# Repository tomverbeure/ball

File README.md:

# FreeCAD to KiCAD PCB outline export

    * Select face that you want as PCB outline
    * Make sure face is aligned with the view
    * With KiCAD StepUp plugin: project selected face to 2D
    * Convert 2D object to sketch
    * Export sketch to PCB layer

    * [Arranging PCB components in a circle with a script](http://kevincuzner.com/2017/04/28/arranging-components-in-a-circle-with-kicad/)

* Postprocessing

    * Chamfer alignment stickouts at the bottom (0.8mm)
    * Chamfer bottom of the triangle (1mm)
    * Fillet the 3 corners of the triangle (1mm)

# LED Sphere

* Isosahedron: 20 triangular faces

   Progression: 1, 1+3 = 4, 4 + 5 = 9, 9 + 7 = 16, 16 + 9 = 25, 25 + 11 = 36, 36 + 13 = 49

   * 1 triangle -> 1 triangle:    20 faces
   * 1 triangle -> 4 triangles:   80 faces
   * 1 triangle -> 9 triangles:  180 faces
   * 1 triangle -> 16 triangles: 320 faces
   * 1 triangle -> 25 triangles: 500 faces

Possibilities:

    * 80 faces, but divide each face into 16 LEDs -> 1280 LEDs
    * 80 faces, but divide each face into 25 LEDs -> 2000 LEDs
    * 80 faces, but divide each face into 36 LEDs -> 2880 LEDs
    * 80 faces, but divide each face into 49 LEDs -> 3920 LEDs

* 20 faces printed.

	* 2-sided triangle: 3  LEDs -> 60 LEDs
	* 3-sided triangle: 6  LEDs -> 120 LEDs
	* 4-sided triangle: 10 LEDs -> 200 LEDs
	* 5-sided triangle: 15 LEDs -> 300 
	* 6-sided triangle: 21 LEDs -> 420
	* 7-sided triangle: 27 LEDs -> 540
	* 8-sided triangle: 35 LEDs -> 700 

# Plug-in LEDs

* WS2812D-F8: $0.11 for 100+  

	* inner diameter: 8.0mm, outer diameter: 9.2mm
 	* [datasheet](https://datasheet.lcsc.com/lcsc/1811021523_Worldsemi-WS2812D-F8_C139126.pdf)
	* [LCSC](https://lcsc.com/product-detail/Light-Emitting-Diodes-span-style-background-color-ff0-LED-span_Worldsemi-WS2812D-F8_C139126.html)
	* 3.5V -> 5.3V
	* Needs capacitor and 75 Ohm resistor between VDD/GND per LED

* [75Ohm resistor](https://lcsc.com/product-detail/Chip-Resistor-Surface-Mount_FOJAN-FRC0603J750-TS_C2907204.html)
* [100nF cap](https://lcsc.com/product-detail/Multilayer-Ceramic-Capacitors-MLCC-SMD-SMT_FH-Guangdong-Fenghua-Advanced-Tech-0603B104K250NT_C694249.html)

# References

* [Geodesic(k) LED Spheres](https://blog.arduino.cc/2020/09/21/these-rgb-led-geodesic-spheres-are-stunning/)

    * [Build instructions](https://www.prusaprinters.org/prints/40182-geodesick-rgb-led-spheres)

* [Construct an icosahedron](https://www.youtube.com/watch?v=biq_SXjaoRU)

* [Construct an icosahedron in FreeCAD](https://www.youtube.com/watch?v=1VXpUjMM-_c)

* [Construction of regular icosahedron within a given sphere](https://proofwiki.org/wiki/Construction_of_Regular_Icosahedron_within_Given_Sphere)

    "From this it is manifest that the square on the diameter of the sphere is five times 
    the square on the radius of the circle from which the icosahedron has been described, 
    and that the diameter of the sphere is composed of the side of the pentagon and two of 
    the sides of the decagon inscribed in the same circle."

    Dsphere^2 = 5 * (Rpent^2)

    Rpent = sqrt(Dsphere^2/5) = Dsphere/sqrt(5) = 2 * Rsphere / sqrt(5)

* [Ad Quadratum Construction and Study of the Regular Polyhedra](http://www.lemeestudies.com/Misc/14.millennium_sphere/products/AdQuadratum.pdf)

* [Freecad scripting tutorial](https://wiki.freecadweb.org/Python_scripting_tutorial)

* [Freecad Topological data scripting](https://wiki.freecadweb.org/Topological_data_scripting)

# FreeCAD comments

* Base.Vector getAngle -> radians, all other functions -> degrees
* Simply viewing actions, such as aligning view to face are not present out of the box
* aligning a object along an axis is broken.
* Location of buttons in the toolbar always changes
* Add spheres for orientation
* FreeCAD over OpenSCAD: interactivity
* The number of LEDs must be chosen so that there's room in the center for a screw.

* When doing an align operation on a object that was created by an assembly of multiple identical components, 
  first create a Compound of it in Part.  Otherwise, the align seems to happen on the main component, not on the
  additional copies.

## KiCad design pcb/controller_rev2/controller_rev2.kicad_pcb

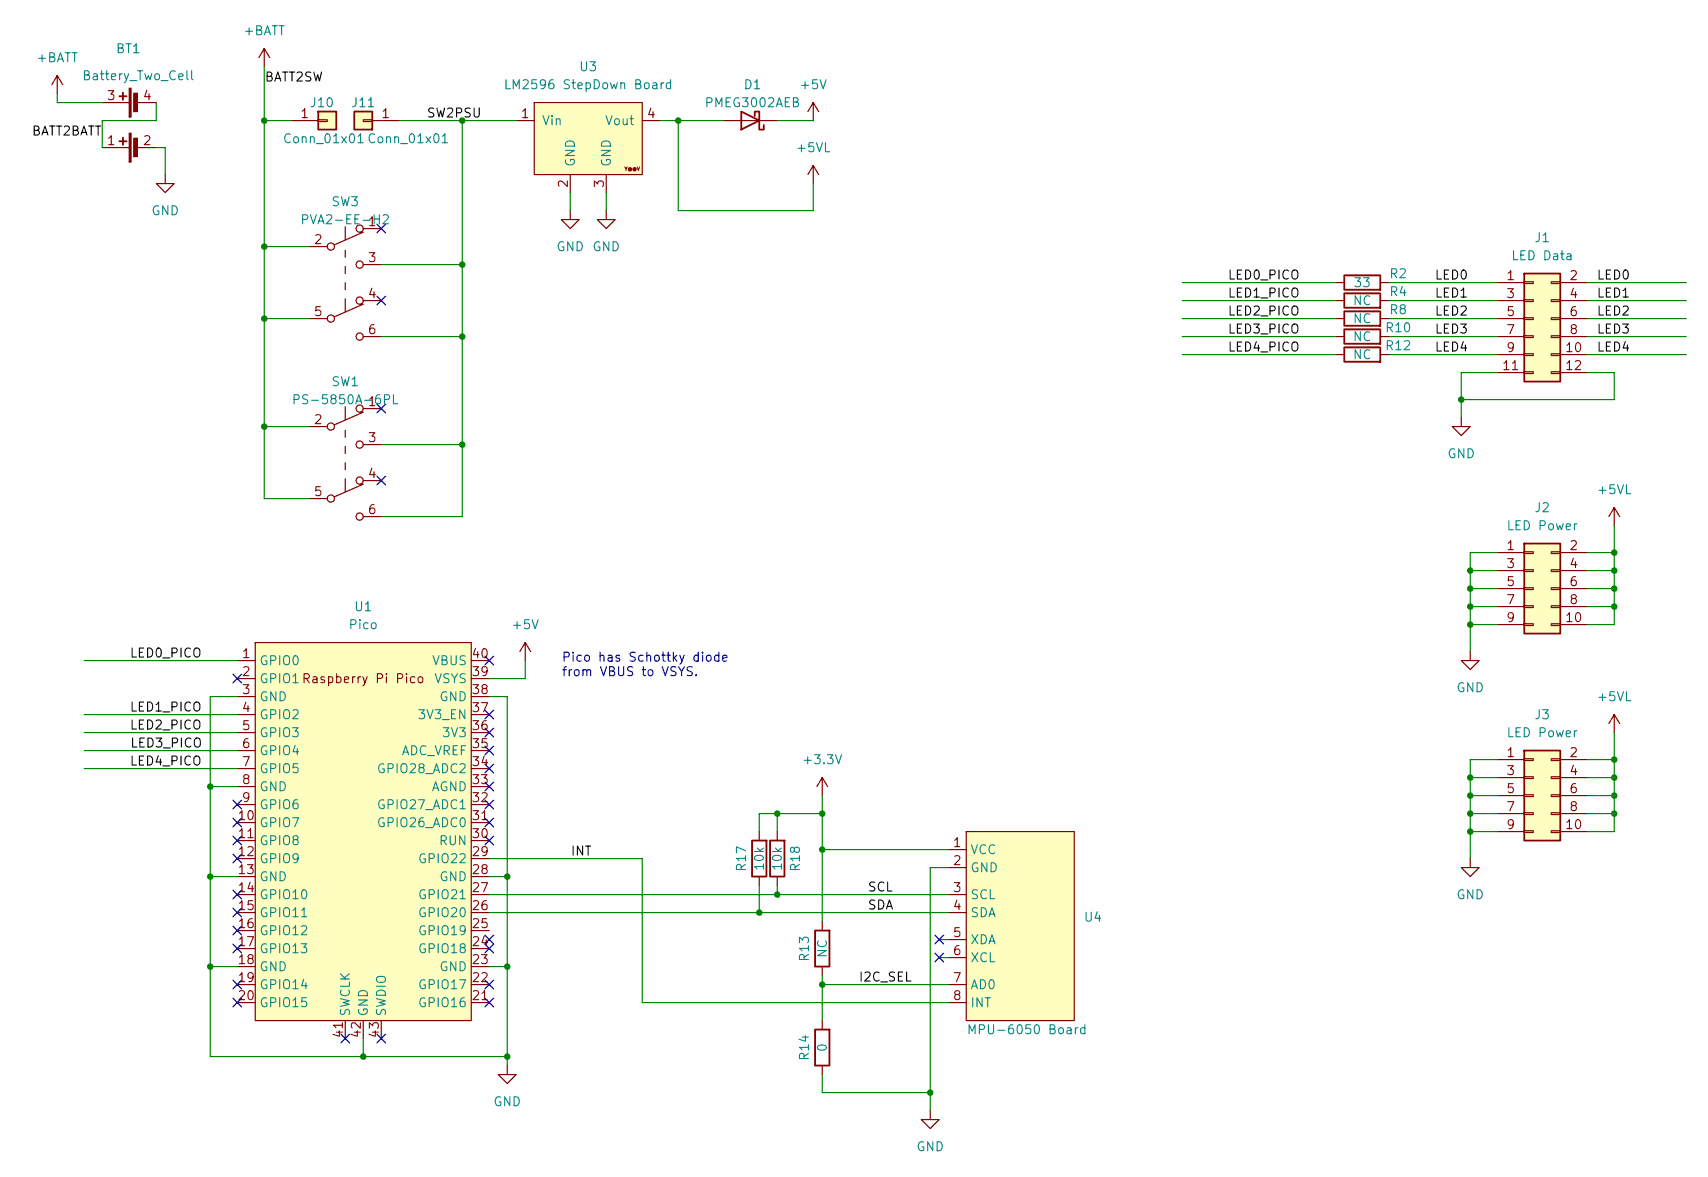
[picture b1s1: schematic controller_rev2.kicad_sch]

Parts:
BT1: Battery_Two_Cell; battery_holder
D1: PMEG3002AEB; D_SOD-523
J1: LED Data; PinHeader_2x06_P2.54mm_Vertical_SMD
J2, J3: LED Power; PinHeader_2x05_P2.54mm_Vertical_SMD
J10, J11: Conn_01x01; TestPoint_Loop_D3.80mm_Drill2.0mm
R2: 33; R_0603_1608Metric_Pad0.98x0.95mm_HandSolder
R4, R8, R10, R12, R13: NC; R_0603_1608Metric_Pad0.98x0.95mm_HandSolder
R14: 0; R_0603_1608Metric_Pad0.98x0.95mm_HandSolder
R17, R18: 10k; R_0603_1608Metric_Pad0.98x0.95mm_HandSolder
SW1: PS-5850A-6PL; SW_Push_2P2T_Toggle_G_Switch-PS-5850A-6PL
SW3: PVA2-EE-H2; SW_Push_2P2T_Toggle_CK_PVA2xxH2xxxxxxV2
U1: Pico; RPi_Pico_SMD_TH
U3: LM2596 StepDown Board; YAAJ_DCDC_StepDown_LM2596
U4: MPU-6050 Board; MPU-6050_Board_no_screw_holes

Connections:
+3V3: R13.2, R17.2, R18.2, U4.1 (VCC)
+5V: D1.1 (K), U1.39 (VSYS)
+5VL: D1.2 (A), J2.2, J2.4, J2.6, J2.8, J2.10, J3.2, J3.4, J3.6, J3.8, J3.10, U3.4 (Vout)
+BATT: BT1.3 (+), J10.1, SW1.2 (B), SW1.5 (B), SW3.2 (B), SW3.5 (B)
/BATT2BATT: BT1.1 (+), BT1.4 (-)
/I2C_SEL: R13.1, R14.2, U4.7 (AD0)
/INT: U1.29 (GPIO22), U4.8 (INT)
/LED0: J1.1, J1.2, R2.2
/LED0_PICO: R2.1, U1.1 (GPIO0)
/LED1: J1.3, J1.4, R4.2
/LED1_PICO: R4.1, U1.4 (GPIO2)
/LED2: J1.5, J1.6, R8.2
/LED2_PICO: R8.1, U1.5 (GPIO3)
/LED3: J1.7, J1.8, R10.2
/LED3_PICO: R10.1, U1.6 (GPIO4)
/LED4: J1.9, J1.10, R12.2
/LED4_PICO: R12.1, U1.7 (GPIO5)
/SCL: R18.1, U1.27 (GPIO21), U4.3 (SCL)
/SDA: R17.1, U1.26 (GPIO20), U4.4 (SDA)
/SW2PSU: J11.1, SW1.3 (C), SW1.6 (C), SW3.3 (C), SW3.6 (C), U3.1 (Vin)
GND: BT1.2 (-), J1.11, J1.12, J2.1, J2.3, J2.5, J2.7, J2.9, J3.1, J3.3, J3.5, J3.7, J3.9, R14.1, U1.3 (GND), U1.8 (GND), U1.13 (GND), U1.18 (GND), U1.23 (GND), U1.28 (GND), U1.38 (GND), U1.42 (GND), U3.2 (GND), U3.3 (GND), U4.2 (GND)

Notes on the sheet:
Pico has Schottky diode from VBUS to VSYS.

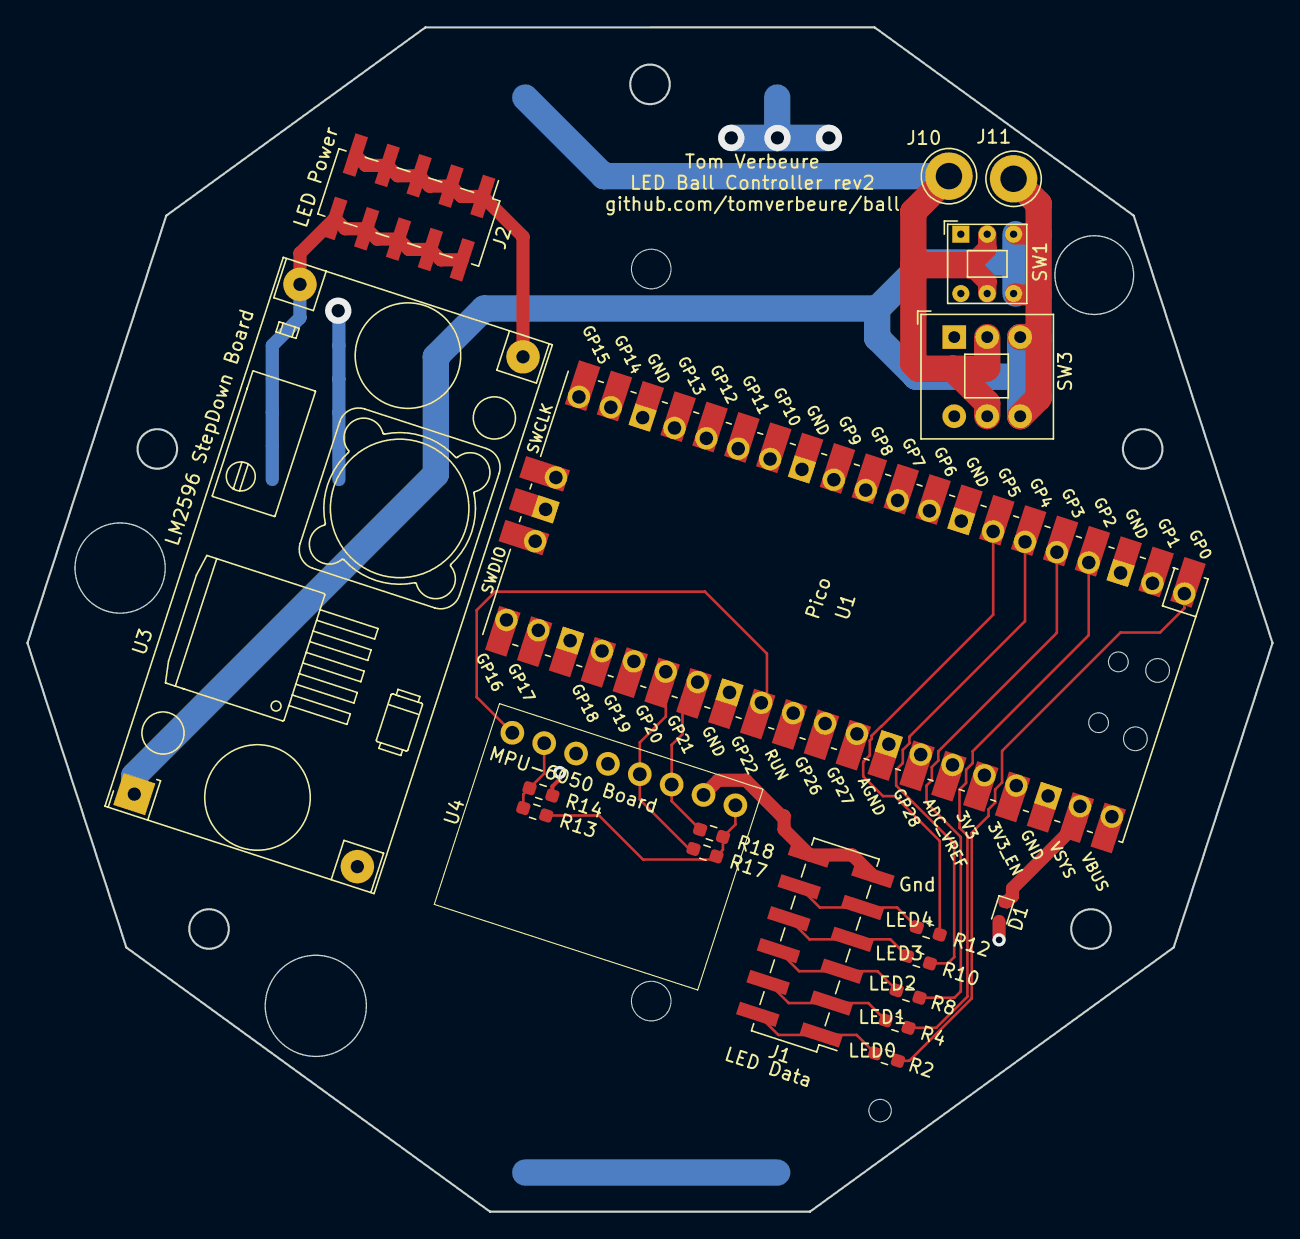
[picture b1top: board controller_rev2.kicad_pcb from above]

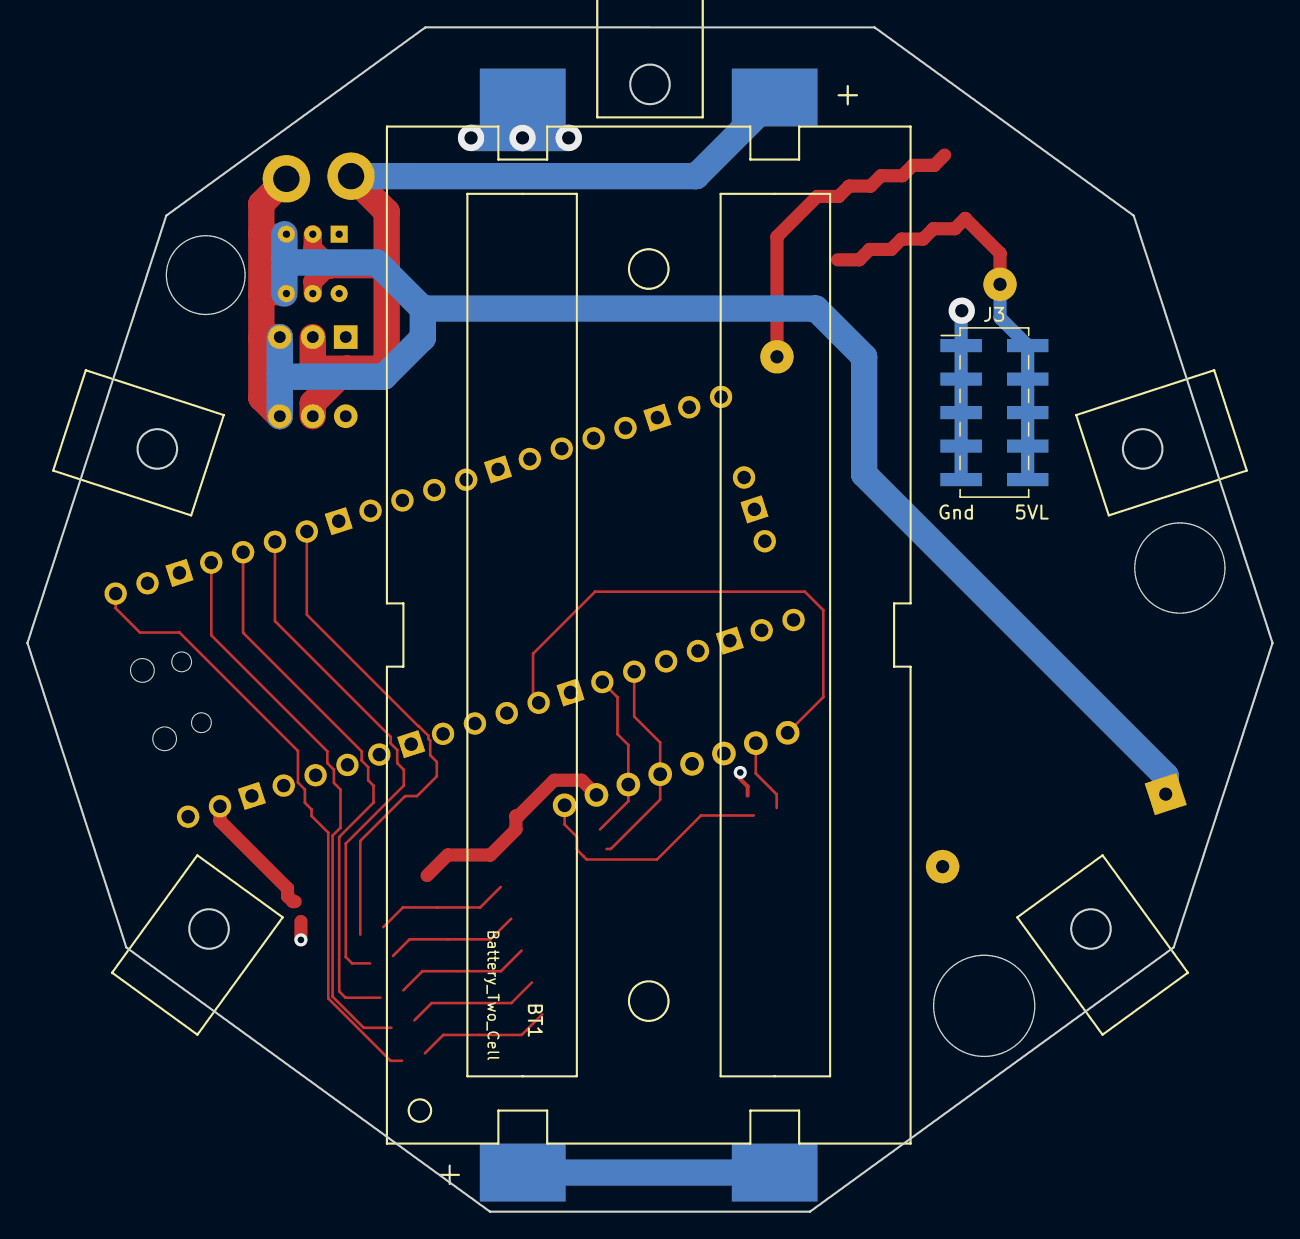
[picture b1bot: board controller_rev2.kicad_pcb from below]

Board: 4 copper layers, 94.4 x 89.8 mm, 21 parts (2 on the bottom side), 21 nets.

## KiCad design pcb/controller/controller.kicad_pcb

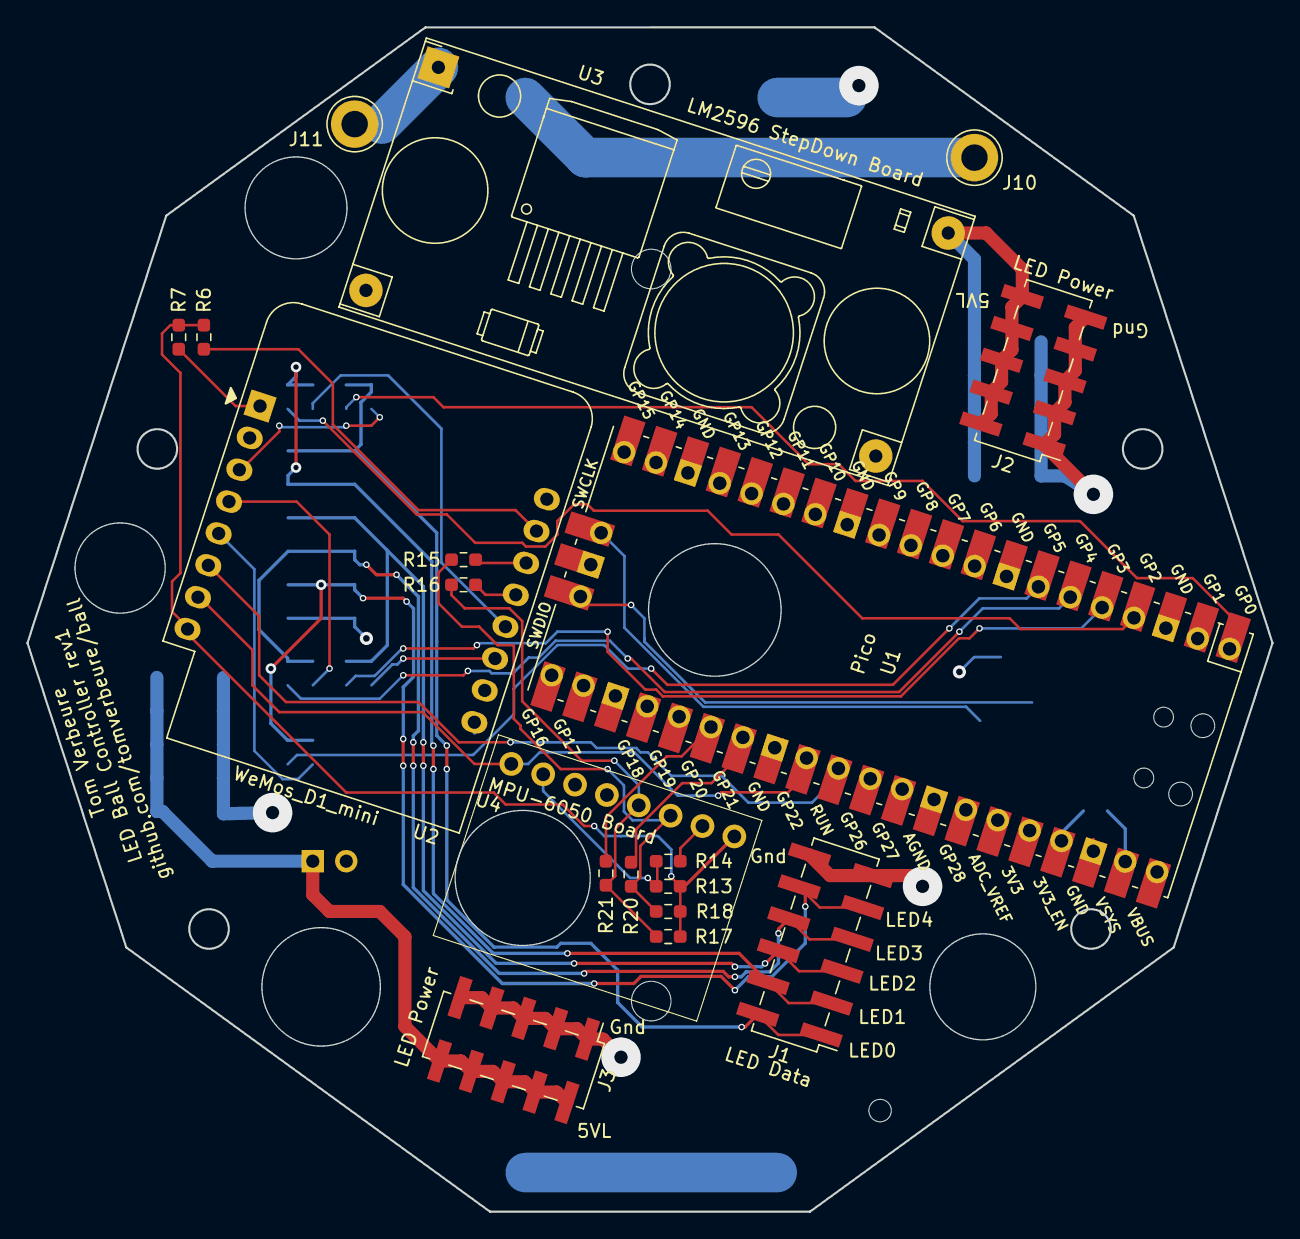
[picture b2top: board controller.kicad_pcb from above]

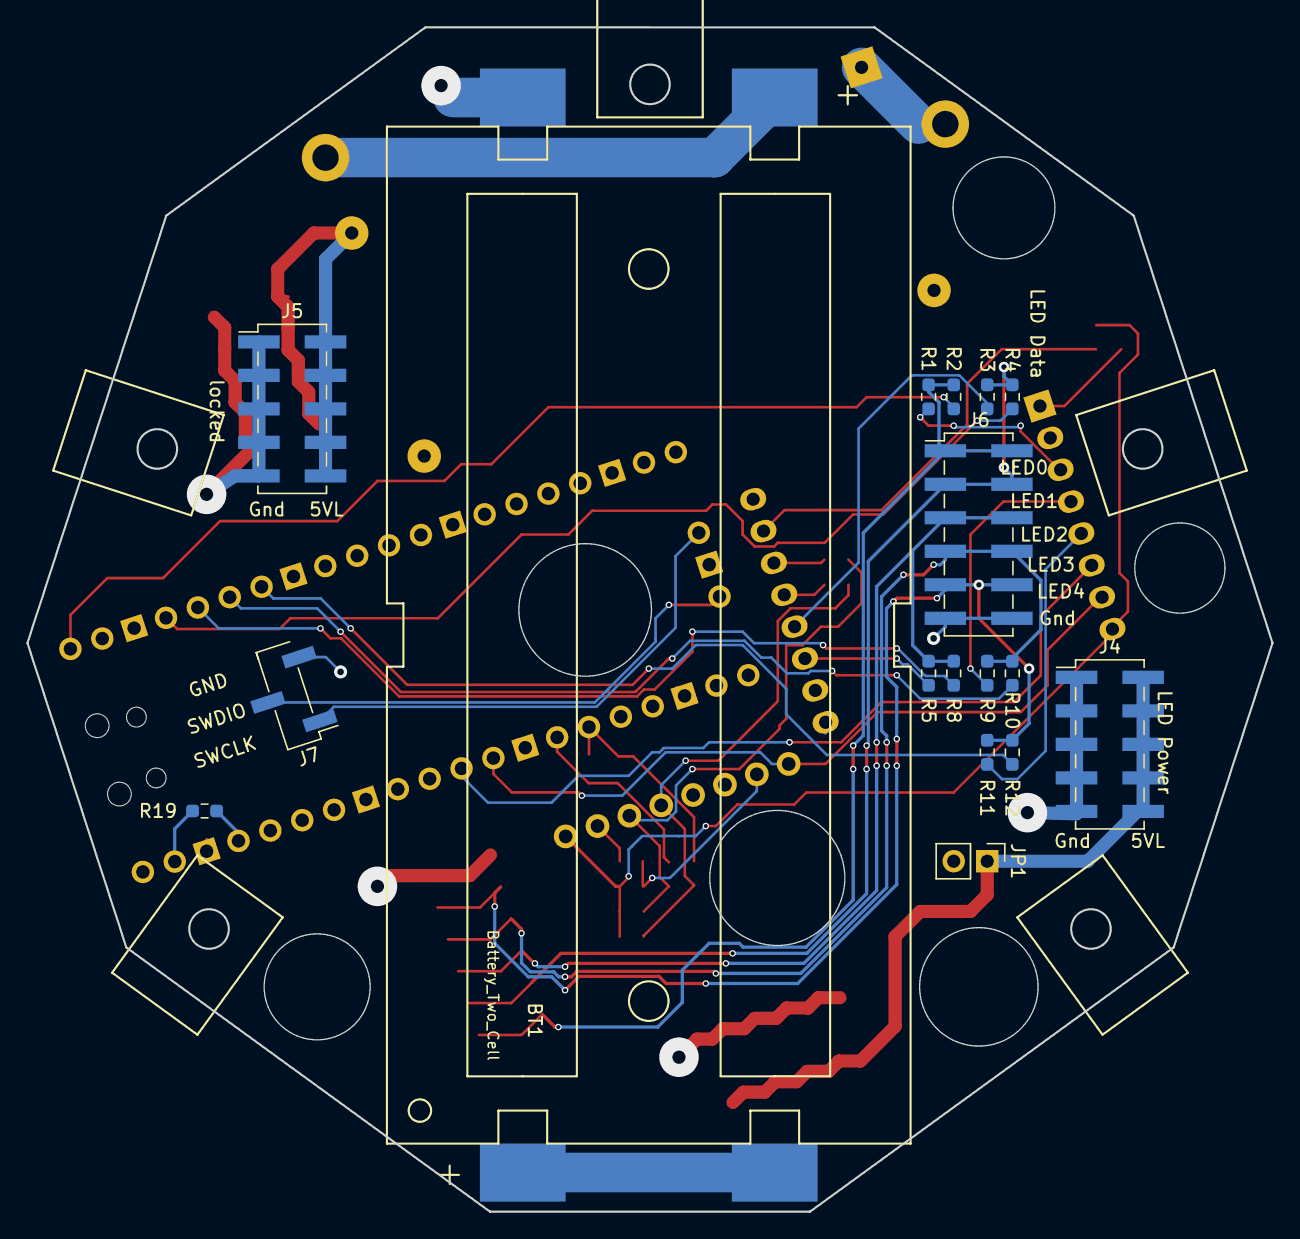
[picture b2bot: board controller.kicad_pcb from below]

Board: 4 copper layers, 94.4 x 89.8 mm, 36 parts (17 on the bottom side), 37 nets.

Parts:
BT1: Battery_Two_Cell; battery_holder
J1, J6: LED Data; PinHeader_2x06_P2.54mm_Vertical_SMD
J2, J3, J4: LED Power; PinHeader_2x05_P2.54mm_Vertical_SMD
J5: locked; PinHeader_2x05_P2.54mm_Vertical_SMD
J7: Conn_01x03_Male; PinHeader_1x03_P2.54mm_Vertical_SMD_Pin1Left
J10, J11: Conn_01x01; TestPoint_Loop_D3.80mm_Drill2.0mm
JP1: 5V Power; PinHeader_1x02_P2.54mm_Vertical
R1, R2, R3, R4, R5, R6, R7, R8, R9, R10, R11, R12, R13, R14, R17, R18: R; R_0603_1608Metric_Pad0.98x0.95mm_HandSolder
R15, R16, R19, R20, R21: 100K; R_0603_1608Metric_Pad0.98x0.95mm_HandSolder
U1: Pico; RPi_Pico_SMD_TH
U2: WeMos_D1_mini; WEMOS_D1_mini_light
U3: LM2596 StepDown Board; YAAJ_DCDC_StepDown_LM2596
U4: MPU-6050 Board; MPU-6050_Board_no_screw_holes

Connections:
+3V3: R6.1, R7.1, R13.2, R17.2, R18.2, U2.8 (3V3), U4.1 (VCC)
+5V: JP1.2 (B), U1.40 (VBUS), U2.9 (5V)
+5VL: J2.2, J2.4, J2.6, J2.8, J2.10, J3.2, J3.4, J3.6, J3.8, J3.10, J4.2, J4.4, J4.6, J4.8, J4.10, J5.2, J5.4, J5.6, J5.8, J5.10, JP1.1 (A), U3.4 (Vout)
+BATT: BT1.3 (+), J10.1
/BATT2BATT: BT1.1 (+), BT1.4 (-)
/INT: U1.29 (GPIO22), U2.7 (CS/D8), U4.8 (INT)
/LED0: J1.1, J1.2, J6.1, J6.2, R1.2, R2.2
/LED0_ESP: R1.1, U2.3 (D0)
/LED0_PICO: R2.1, U1.1 (GPIO0)
/LED1: J1.3, J1.4, J6.3, J6.4, R3.2, R4.2
/LED1_ESP: R3.1, U2.12 (D3)
/LED1_PICO: R4.1, U1.4 (GPIO2)
/LED2: J1.5, J1.6, J6.5, J6.6, R5.2, R8.2
/LED2_ESP: R5.1, U2.11 (D4)
/LED2_PICO: R8.1, U1.5 (GPIO3)
/LED3: J1.7, J1.8, J6.7, J6.8, R9.2, R10.2
/LED3_ESP: R9.1, U2.4 (SCK/D5)
/LED3_PICO: R10.1, U1.6 (GPIO4)
/LED4: J1.9, J1.10, J6.9, J6.10, R11.2, R12.2
/LED4_ESP: R11.1, U2.5 (MISO/D6)
/LED4_PICO: R12.1, U1.7 (GPIO5)
/PICO_RUN: U1.30 (RUN), U2.6 (MOSI/D7)
/SCL: R15.1, R18.1, R20.1, U4.3 (SCL)
/SDA: R16.1, R17.1, R21.1, U4.4 (SDA)
/SW2PSU: J11.1, U3.1 (Vin)
/SWCLK: J7.1, U1.41 (SWCLK)
/SWDIO: J7.2, U1.43 (SWDIO)
GND: BT1.2 (-), J1.11, J1.12, J2.1, J2.3, J2.5, J2.7, J2.9, J3.1, J3.3, J3.5, J3.7, J3.9, J4.1, J4.3, J4.5, J4.7, J4.9, J5.1, J5.3, J5.5, J5.7, J5.9, J6.11, J6.12, J7.3, R14.1, U1.3 (GND), U1.8 (GND), U1.18 (GND), U1.23 (GND), U1.28 (GND), U1.38 (GND), U1.42 (GND), U2.10 (GND), U3.2 (GND), U3.3 (GND), U4.2 (GND)
unnamed: R6.2, U2.15 (RX)
unnamed: R7.2, U2.1 (~RST)
unnamed: R13.1, R14.2, U4.7 (AD0)
unnamed: R15.2, U2.14 (SCL/D1)
unnamed: R16.2, U2.13 (SDA/D2)
unnamed: R19.1, U1.39 (VSYS)
unnamed: R19.2, U1.37 (3V3_EN)
unnamed: R20.2, U1.27 (GPIO21)
unnamed: R21.2, U1.26 (GPIO20)

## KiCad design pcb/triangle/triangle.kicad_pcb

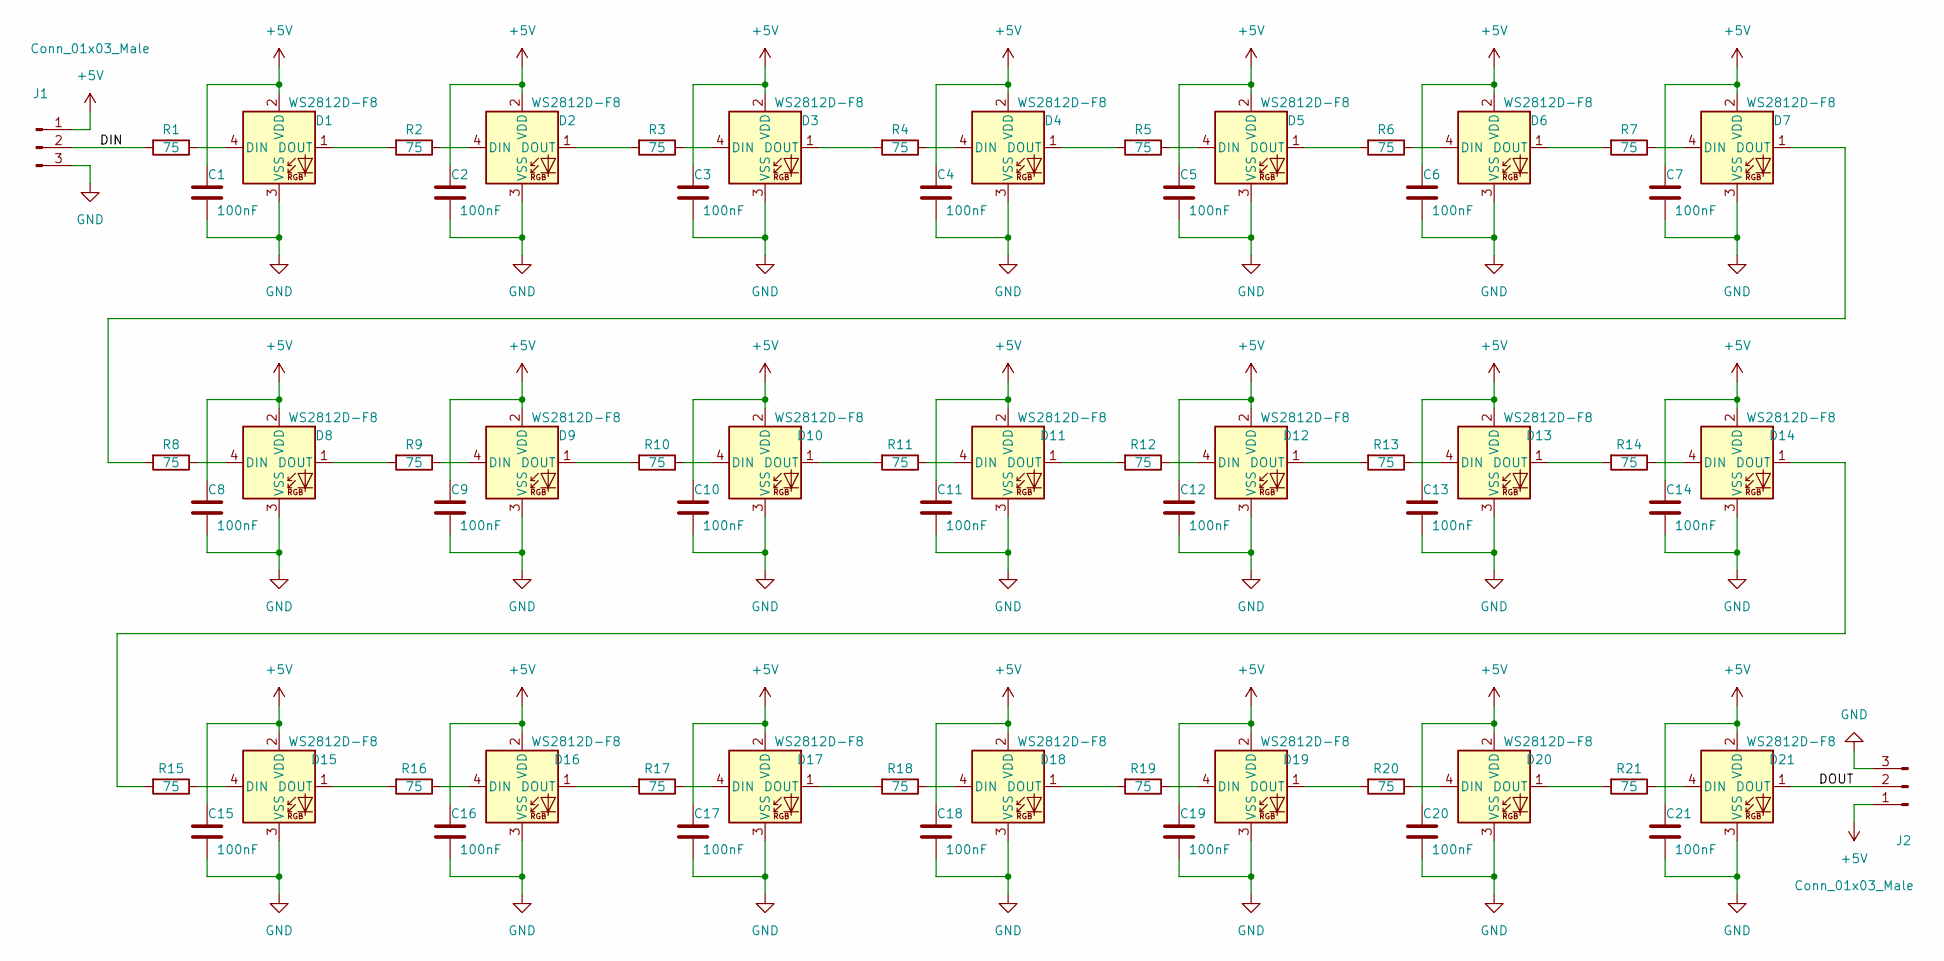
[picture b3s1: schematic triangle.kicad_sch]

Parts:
C1, C2, C3, C4, C5, C6, C7, C8, C9, C10, C11, C12, C13, C14, C15, C16, C17, C18, C19, C20, C21: 100nF; C_0603_1608Metric
D1, D2, D3, D4, D5, D6, D7, D8, D9, D10, D11, D12, D13, D14, D15, D16, D17, D18, D19, D20, D21: WS2812D-F8; LED_D8.0mm-4
J1, J2: Conn_01x03_Male; PinHeader_1x03_P2.54mm_Vertical
R1, R2, R3, R4, R5, R6, R7, R8, R9, R10, R11, R12, R13, R14, R15, R16, R17, R18, R19, R20, R21: 75; R_0603_1608Metric

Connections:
+5V: C1.1, C2.1, C3.1, C4.1, C5.1, C6.1, C7.1, C8.1, C9.1, C10.1, C11.1, C12.1, C13.1, C14.1, C15.1, C16.1, C17.1, C18.1, C19.1, C20.1, C21.1, D1.2 (VDD), D2.2 (VDD), D3.2 (VDD), D4.2 (VDD), D5.2 (VDD), D6.2 (VDD), D7.2 (VDD), D8.2 (VDD), D9.2 (VDD), D10.2 (VDD), D11.2 (VDD), D12.2 (VDD), D13.2 (VDD), D14.2 (VDD), D15.2 (VDD), D16.2 (VDD), D17.2 (VDD), D18.2 (VDD), D19.2 (VDD), D20.2 (VDD), D21.2 (VDD), J1.1, J2.1
/DIN: J1.2, R1.2
/DOUT: D21.1 (DOUT), J2.2
GND: C1.2, C2.2, C3.2, C4.2, C5.2, C6.2, C7.2, C8.2, C9.2, C10.2, C11.2, C12.2, C13.2, C14.2, C15.2, C16.2, C17.2, C18.2, C19.2, C20.2, C21.2, D1.3 (VSS), D2.3 (VSS), D3.3 (VSS), D4.3 (VSS), D5.3 (VSS), D6.3 (VSS), D7.3 (VSS), D8.3 (VSS), D9.3 (VSS), D10.3 (VSS), D11.3 (VSS), D12.3 (VSS), D13.3 (VSS), D14.3 (VSS), D15.3 (VSS), D16.3 (VSS), D17.3 (VSS), D18.3 (VSS), D19.3 (VSS), D20.3 (VSS), D21.3 (VSS), J1.3, J2.3
unnamed: D1.1 (DOUT), R2.2
unnamed: D1.4 (DIN), R1.1
unnamed: D2.1 (DOUT), R3.2
unnamed: D2.4 (DIN), R2.1
unnamed: D3.1 (DOUT), R4.2
unnamed: D3.4 (DIN), R3.1
unnamed: D4.1 (DOUT), R5.2
unnamed: D4.4 (DIN), R4.1
unnamed: D5.1 (DOUT), R6.2
unnamed: D5.4 (DIN), R5.1
unnamed: D6.1 (DOUT), R7.2
unnamed: D6.4 (DIN), R6.1
unnamed: D7.1 (DOUT), R8.2
unnamed: D7.4 (DIN), R7.1
unnamed: D8.1 (DOUT), R9.2
unnamed: D8.4 (DIN), R8.1
unnamed: D9.1 (DOUT), R10.2
unnamed: D9.4 (DIN), R9.1
unnamed: D10.1 (DOUT), R11.2
unnamed: D10.4 (DIN), R10.1
unnamed: D11.1 (DOUT), R12.2
unnamed: D11.4 (DIN), R11.1
unnamed: D12.1 (DOUT), R13.2
unnamed: D12.4 (DIN), R12.1
unnamed: D13.1 (DOUT), R14.2
unnamed: D13.4 (DIN), R13.1
unnamed: D14.1 (DOUT), R15.2
unnamed: D14.4 (DIN), R14.1
unnamed: D15.1 (DOUT), R16.2
unnamed: D15.4 (DIN), R15.1
unnamed: D16.1 (DOUT), R17.2
unnamed: D16.4 (DIN), R16.1
unnamed: D17.1 (DOUT), R18.2
unnamed: D17.4 (DIN), R17.1
unnamed: D18.1 (DOUT), R19.2
unnamed: D18.4 (DIN), R18.1
unnamed: D19.1 (DOUT), R20.2
unnamed: D19.4 (DIN), R19.1
unnamed: D20.1 (DOUT), R21.2
unnamed: D20.4 (DIN), R20.1
unnamed: D21.4 (DIN), R21.1

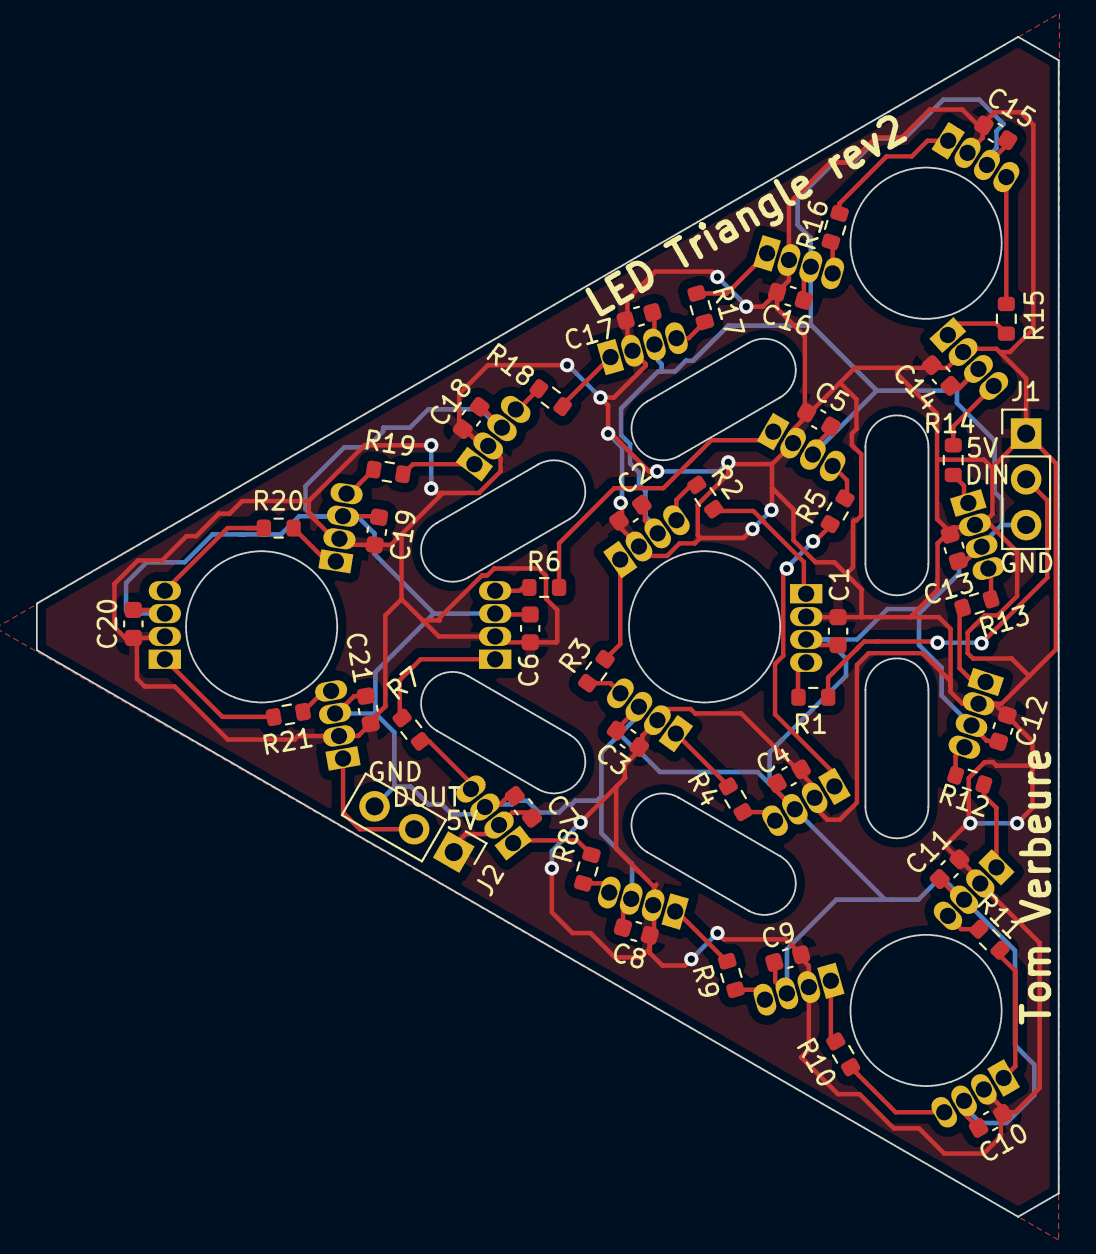
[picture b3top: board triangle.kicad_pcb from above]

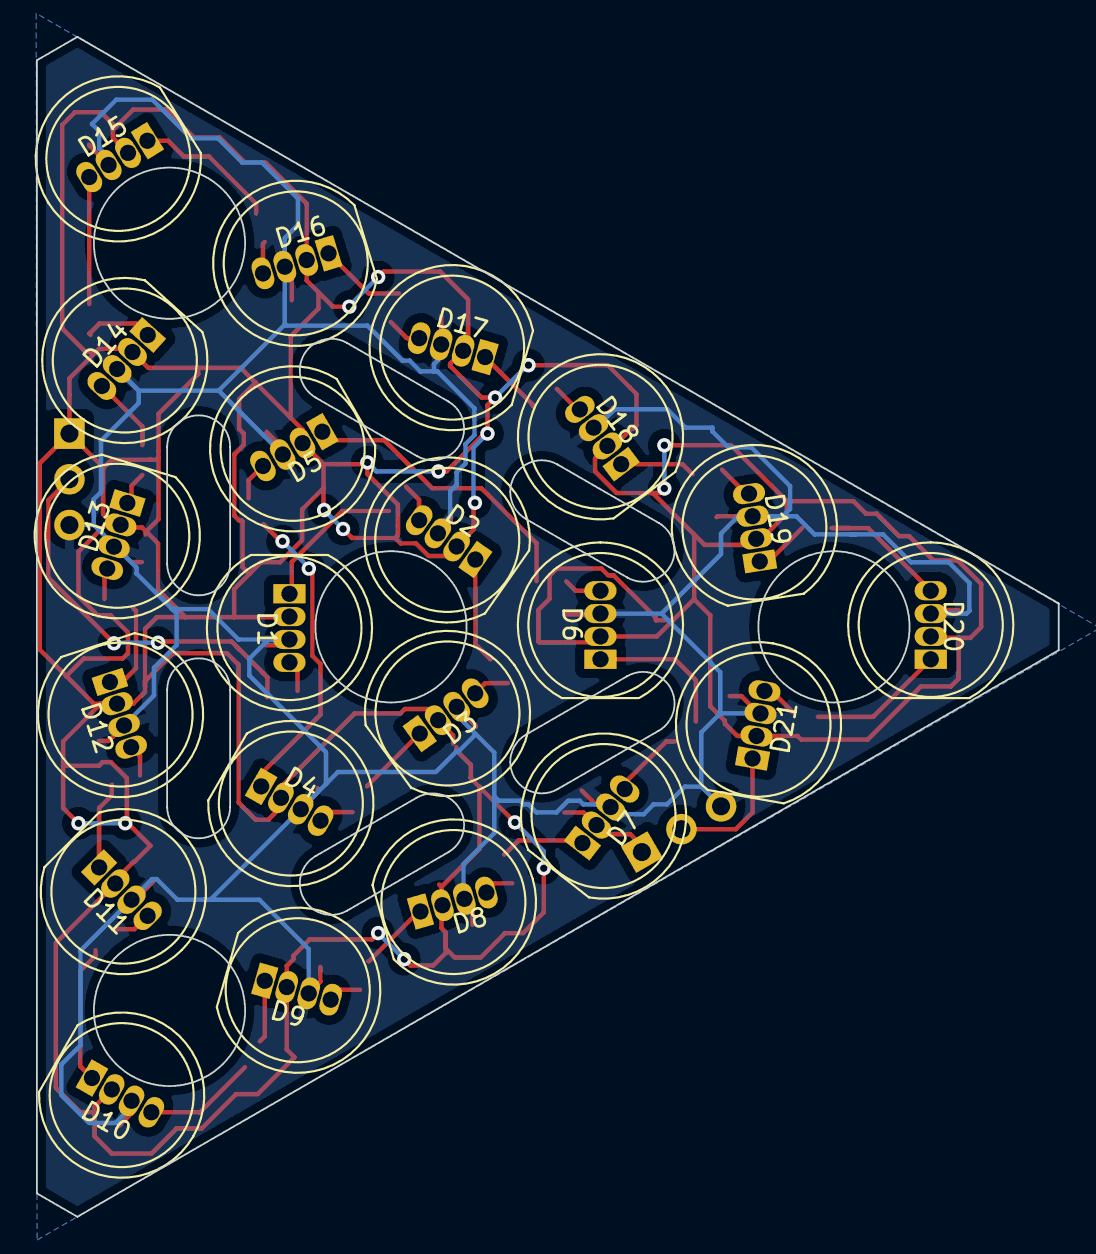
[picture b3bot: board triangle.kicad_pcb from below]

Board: 2 copper layers, 56.8 x 65.5 mm, 65 parts (21 on the bottom side), 45 nets.

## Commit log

2019-09-07 Hexagon
2019-09-07 Add hole.
2019-09-07 Move icosahedron experiment to its own directory.
2019-09-07 C healpix
2019-09-07 Sphere with healpix pixels
2019-09-07 Make sphere green.
2019-09-07 Dots colors per face.
2019-09-08 Patch chealpix for xyv2nest function.
2019-09-08 Polyhedron fail.
2019-09-08 Boundary of face 0.
2019-09-08 4 top cut boundaries.
2019-09-08 Move some code scene_py.py
2019-09-08 Move led rendering to python.
2021-12-22 Assembly with uneven holes. (Use as bad example 1.)
2021-12-22 Move around.
2021-12-22 10 LEDs per face, spread roughly evenly.
2022-01-08 Various trials.
2022-01-09 Radiating screw holes.
2022-01-10 Assembly.
2022-01-18 Start of script.
2022-01-20 Checkpoint. Use Draft.point to rotate.
2022-01-20 Calculate LED locations
2022-01-20 Create LED holes.
2022-01-21 Cut sphere into rounded tetrahedron.
2022-01-22 line plane intersection
2022-01-22 Rotate LED leads gap. WIP.
2022-01-23 Script to iteratively find the right angle.
2022-01-23 Find angle using binary search.
2022-01-23 Add find_correct_angle to main script. WIP.
2022-01-23 find_correct_angle must use x intersection plane, not y.
2022-01-23 Rotate main triangle to be orthogonal to X axis.
2022-01-23 Angles are correct in 1 quadrant.
2022-01-24 Simplify LED rotation.
2022-01-24 Refactor to create_led_locations()
2022-01-24 Refactor into create_triangle_vertices
2022-01-24 Apply stash?
2022-01-24 Apply stash.
2022-01-24 Top half is correct.
2022-01-24 All quadrants are correctly rotated.
2022-01-24 LED shaft parameters.
2022-01-24 Use pcb_plane_offset everywhere.
2022-01-24 Add screw insert holes.
2022-01-31 Add PCB.
2022-02-28 Adjust sizes.
2022-03-01 Freecad to Kicad instructions
2022-03-01 Add extra screw insert in center.
2022-03-03 Typo.
2022-03-03 interlock trial.
2022-03-03 Icosahedron with export to PCB.
2022-03-03 Triangle PCB.
2022-03-03 Magnet holes.
2022-03-03 Move adjustable parameters to top of file.
2022-03-04 Add magnet holes on 1 side.
2022-03-04 Fix magnet radius.
2022-03-04 Magnet holes on 3 sides.
2022-03-04 Alignment features. WIP.
2022-03-05 Magnets and alignments on all 3 sides.
2022-03-05 Move corner insert holes a bit outside and change to magnet holes.
2022-03-05 Ring assembled.
2022-03-05 Circle and Ring+Circle assembly
2022-03-06 Pics.
2022-03-06 Add inner piece feet. Add additional PCB holes.
2022-03-06 Parameterize PCB gap.
2022-03-06 Extruded triangle.
2022-03-08 Create attach point.
2022-03-10 Make slightly larger. Adjust magnet sizes.
2022-03-10 Adjust insert holes a bit towards the center.
2022-03-13 Split PCB one large PCB gap into 2 smaller gaps.
2022-03-13 Shell rev1 files.
2022-03-27 Move triangle v1 gerbers to v1 directory.
2022-03-27 Triangle PCB v2.
2022-03-27 shell gcode, assembly experiments.
2022-03-28 Inner piece, rev1.
2022-03-30 Inner center/left/right pieces
2022-04-04 Battery holder.
2022-04-16 LED & battery holder fixes.
2022-04-16 Commit...
2022-04-17 Add Raspberry Pico to library.
2022-04-17 Link to Pico.wrl.
2022-04-17 Board with only RPico.
2022-04-17 MPU-6050_Board
2022-04-17 LM2596 board in FreeCAD (WIP)
2022-04-17 LM2596 model from GrabCAD
2022-04-30 Move battery holder model.
2022-05-01 Checkpoint after controller gerbers.
2022-06-12 Single sphere element with LEDs cycling color.
2022-06-12 Drive 420 LEDs with rotating pattern.
2022-06-16 Add little spheres where the LED coordinates are.
2022-06-19 Blog post WIP.
2022-06-20 All 20 sphere pieces forming a ball.
2022-06-20 Adjust for correct order of sphere pieces.
2022-06-20 Dump led coordinates to json file.
2022-06-26 Update .gitignore file.
2022-06-26 Move to mpython dir
2022-06-26 Add C ws2812 code, based on pico-examples.
2022-07-06 Preparation for LED coordinate system.
2022-07-06 Coarse triangle mapping.
2022-07-06 LEDs are correctly mapped to virtual coordinate.
2022-07-06 Refactor LED nr calculation.
2022-07-06 Random rings
2022-07-06 Random ring thickness.
2022-07-09 Refactor rings.
2022-07-10 Multipler ring trains.
2022-07-10 Shared max color value.
2022-07-10 Multiple rings in random pattern.
2022-07-10 Refactoring. Particle effect.
2022-07-10 Variable gravity vector.
2022-07-10 Gravity particles.
2022-07-17 Pattern class. Refactor Rings effect into Pattern.
2022-07-17 Pride flag.
2022-07-17 RGB sphere, sparkles
2022-07-17 Add rotation to RGB sphere.
2022-07-22 Dump LED positions to file.
2022-11-05 Loop between different effects. Disable broken RGB sphere.
2022-11-05 Add #defines for effects.
2022-11-06 All effects are working. Frozen images.
2023-05-22 Controller rev2.
